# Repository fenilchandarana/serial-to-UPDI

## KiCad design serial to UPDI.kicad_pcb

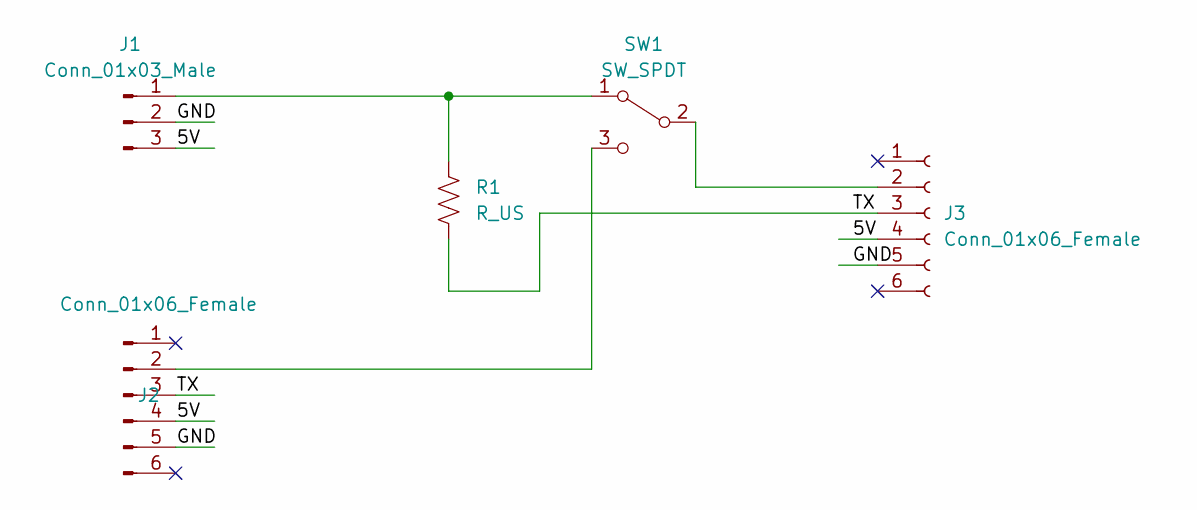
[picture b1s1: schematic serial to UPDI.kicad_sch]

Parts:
J1: Conn_01x03_Male; PinHeader_1x03_P2.54mm_Vertical
J2, J3: Conn_01x06_Female; PinHeader_1x06_P2.54mm_Vertical
R1: R_US; R_Axial_DIN0204_L3.6mm_D1.6mm_P7.62mm_Horizontal
SW1: SW_SPDT; PinHeader_1x03_P2.54mm_Vertical

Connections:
/5V: J1.3, J2.4, J3.4
/GND: J1.2, J2.5, J3.5
/TX: J2.3, J3.3, R1.2
unnamed: J1.1, R1.1, SW1.1 (A)
unnamed: J2.2, SW1.3 (C)
unnamed: J3.2, SW1.2 (B)

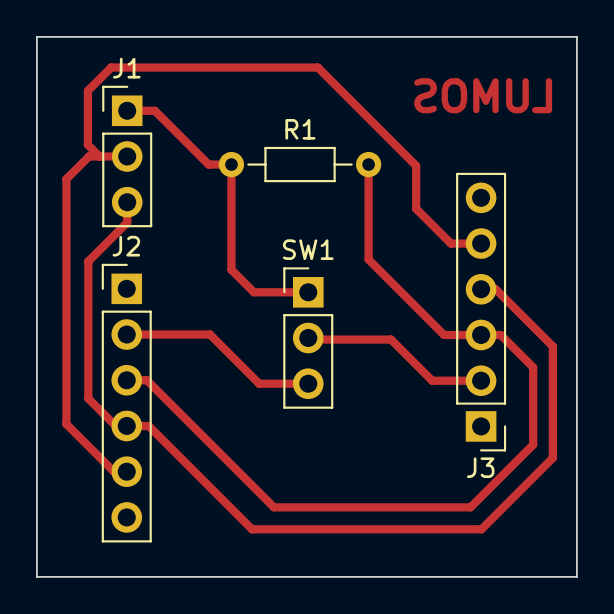
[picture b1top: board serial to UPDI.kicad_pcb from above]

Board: 2 copper layers, 30.0 x 30.0 mm, 5 parts (0 on the bottom side), 6 nets.

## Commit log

2023-10-10 initial commit. blank project
2023-10-13 designed schematic and board file for serial to UPDI converter. genrated gerber and egx files for fabricating the pcb in micromilling machine
2024-08-25 some changes in the backup folder
